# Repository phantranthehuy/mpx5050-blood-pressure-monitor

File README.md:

# 🩺 Digital Oscillometric Blood Pressure Monitor

> An academic research project focused on designing and developing a digital blood pressure monitor using the **MPX5050** pressure sensor and the **Oscillometric Method**.

## 📖 Table of Contents
- [About the Project](#about-the-project)
- [Key Features](#key-features)
- [Team Members](#team-members)
- [System Architecture](#system-architecture)
- [Technology Stack](#technology-stack)
- [Repository Structure](#repository-structure)
- [Getting Started](#getting-started)
- [License](#license)

## 🔬 About the Project
This repository contains the hardware schematics, embedded C firmware, and signal processing algorithms for an automated blood pressure monitor. 

The system operates based on the **Oscillometric Method**. It extracts tiny pressure oscillations (AC component) superimposed on the static cuff pressure (DC component) during the deflation phase. By analyzing the envelope of these oscillations, the system calculates the Mean Arterial Pressure (MAP), Systolic Pressure (SYS), Diastolic Pressure (DIA), and Heart Rate (BPM).

## ✨ Key Features
- **Automated Cuff Control:** Smooth inflation and linear deflation using a DC pump and a solenoid valve.
- **High-Precision Sensing:** Utilizes the MPX5050DP sensor with a custom Analog Front-End (AFE) for signal amplification and band-pass filtering (0.5Hz - 5Hz).
- **DSP Algorithms:** Implements digital filtering and envelope detection algorithms to accurately identify blood pressure parameters.
- **User Interface:** Real-time pressure monitoring and final result display via an LCD/OLED screen.

## 👥 Team Members
| Name | Role | Responsibilities |
| :--- | :--- | :--- |
| **Phan Tran The Huy** | **Project Manager & Hardware Lead** | Overall project management, Altium/KiCad schematic & PCB design, and hardware integration. |
| **Tran Nhat Ly** | **Mechanical & UI/UX Engineer** | 3D enclosure design, mechanical assembly, component sourcing, and UI programming. |
| **Nguyen Huy Hoang** | **DSP Algorithm & Research Lead** | Signal processing research (Kalman/FIR filters), data analysis, and technical documentation. |
| **Cao Hoang Tung** | **Embedded Software Engineer** | STM32 C programming, Pump/Valve driver implementation, and translating MATLAB/Python algorithms into embedded C. |

## 📐 System Architecture

The core of the system relies on capturing and separating the pressure signals:

## 🛠 Technology Stack
- **Microcontroller:** STM32 Series
- **Firmware:** C (STM32 HAL, CMake) trong `firmware/stm32-hal-cmake/`; tùy chọn C/C++ Arduino (STM32duino) trong `firmware/stm32-arduino-pio/`.
- **Development Environment:** VS Code with STM32CubeIDE Extension (HAL) hoặc VS Code + PlatformIO (Arduino, `firmware/stm32-arduino-pio/`).
- **Hardware Design:** Altium Designer / KiCad
- **Simulation Tools:** LTSpice (Analog filtering), Python/MATLAB (Algorithm verification)

## 📂 Repository Structure
```text
📦 mpx5050-blood-pressure-monitor
 ┣ 📂 Algorithms      # Python/MATLAB scripts for algorithm simulation & signal filtering
 ┣ 📂 Docs            # Datasheets, academic papers, and technical reports
 ┣ 📂 firmware        # stm32-hal-cmake (CMake+HAL) + stm32-arduino-pio (PlatformIO Arduino)
 ┣ 📂 Hardware        # Schematics, PCB layouts, and Bill of Materials (BOM)
 ┣ 📂 Mechanical      # 3D models and CAD files for the device enclosure
 ┣ 📜 .gitignore      # Ignored files for STM32, VS Code, and EDA tools
 ┣ 📜 LICENSE         # MIT License
 ┗ 📜 README.md       # Project documentation
```

## 🚀 Getting Started

### Prerequisites
- **VS Code** installed with the `C/C++` and `STM32 VS Code Extension`.
- **STM32CubeMX** (for modifying microcontroller pinouts/clocks).
- **Git** for version control.

### Installation & Build
1. **Clone the repository:**
   ```bash
   git clone https://github.com/your-username/mpx5050-blood-pressure-monitor.git
   ```
2. **Open the firmware (HAL / CMake):**
   Open the `firmware/stm32-hal-cmake` directory in VS Code (CMake + STM32 HAL).
3. **Optional — Arduino framework (same MCU):**
   Open `firmware/stm32-arduino-pio` in VS Code with the PlatformIO extension, or run `pio run` from that folder (see `firmware/stm32-arduino-pio/README.md`).
4. **Compile:**
   Press `Ctrl + Shift + B` (or use the STM32 extension build button) to compile the C code and generate the `.elf` / `.hex` files.
5. **Flash to MCU:**
   Connect your ST-Link debugger and click `Run > Start Debugging` (F5) to flash the firmware onto the STM32.

## ⚖️ License
This project is licensed under the **MIT License** - see the [LICENSE](LICENSE) file for details. Designed for academic and research purposes.

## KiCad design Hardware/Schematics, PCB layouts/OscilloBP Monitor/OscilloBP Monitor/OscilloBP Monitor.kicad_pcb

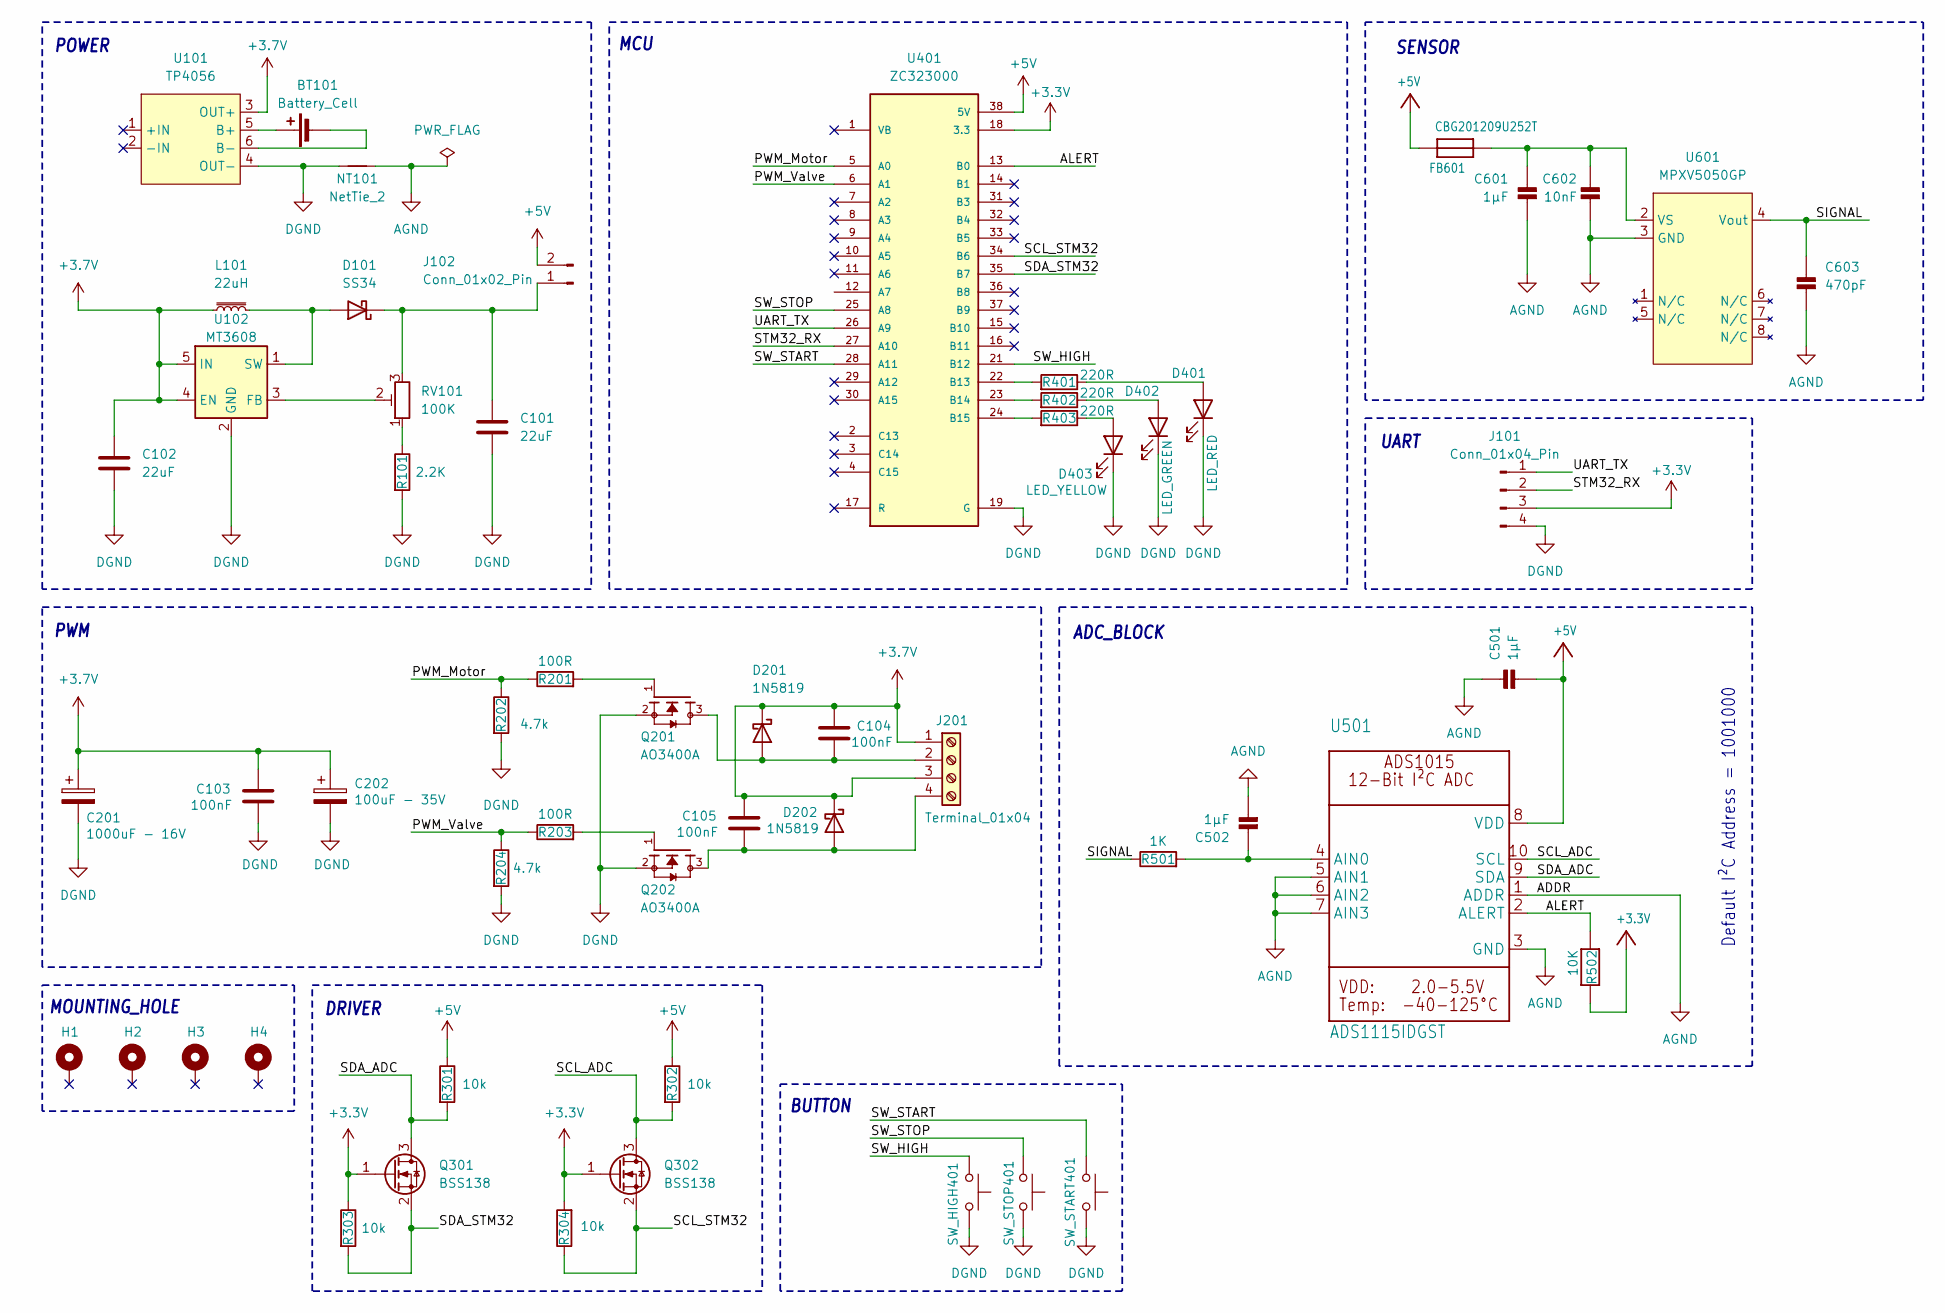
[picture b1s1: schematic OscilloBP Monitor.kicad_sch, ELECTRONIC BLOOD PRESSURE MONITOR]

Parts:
BT101: Battery_Cell; 1x18650
C101, C102: 22uF; C_1206_3216Metric_Pad1.33x1.80mm_HandSolder
C103, C104, C105: 100nF; C_1206_3216Metric_Pad1.33x1.80mm_HandSolder
C201: 1000uF - 16V; CP_Radial_D16.0mm_P7.50mm
C202: 100uF - 35V; CP_Radial_D6.3mm_P2.50mm
C501, C502, C601: 1µF; C_1206_3216Metric_Pad1.33x1.80mm_HandSolder
C602: 10nF; C_1206_3216Metric_Pad1.33x1.80mm_HandSolder
C603: 470pF; C_1206_3216Metric_Pad1.33x1.80mm_HandSolder
D101: SS34; D_SMA
D201, D202: 1N5819; D_DO-41_SOD81_P10.16mm_Horizontal
D401: LED_RED; LED_D3.0mm
D402: LED_GREEN; LED_D3.0mm
D403: LED_YELLOW; LED_D3.0mm
FB601: CBG201209U252T; L_0805_2012Metric_Pad1.05x1.20mm_HandSolder
H1, H2, H3, H4: MountingHole_Pad; mounting
J101: Conn_01x04_Pin; PinHeader_1x04_P2.54mm_Vertical
J102: Conn_01x02_Pin; PinHeader_1x02_P2.54mm_Vertical
J201: Terminal_01x04; PhoenixContact_GMSTBA_2,5_4-G-7,62_1x04_P7.62mm_Horizontal
L101: 22uH; CDRH104
NT101: NetTie_2; NetTie-2_THT_Pad0.3mm
Q201, Q202: AO3400A; SOT95P280X125-3N
Q301, Q302: BSS138; SOT-23
R101: 2.2K; R_1206_3216Metric_Pad1.30x1.75mm_HandSolder
R201, R203: 100R; R_1206_3216Metric_Pad1.30x1.75mm_HandSolder
R202, R204: 4.7k; R_1206_3216Metric_Pad1.30x1.75mm_HandSolder
R301, R302, R303, R304: 10k; R_1206_3216Metric_Pad1.30x1.75mm_HandSolder
R401, R402, R403: 220R; R_1206_3216Metric_Pad1.30x1.75mm_HandSolder
R501: 1K; R_1206_3216Metric_Pad1.30x1.75mm_HandSolder
R502: 10K; R_1206_3216Metric_Pad1.30x1.75mm_HandSolder
RV101: 100K; Potentiometer_Bourns_3296W_Vertical
SW_HIGH401: SW_Push; SW_PUSH_6mm_H4.3mm
SW_START401: SW_Push; SW_PUSH_6mm_H4.3mm
SW_STOP401: SW_Push; SW_PUSH_6mm_H4.3mm
U101: TP4056; TP4056_Module
U102: MT3608; SOT-23-6
U401: ZC323000; STM32F103C8T6; PARTREV N/A
U501: ADS1115IDGST; ADS1115_MSOP10
U601: MPXV5050GP; SOIC127P600X175-8N

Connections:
+3.3V: J101.3, Q301.1 (G), Q302.1 (G), R303.1, R304.2, R502.2, U401.18 (3.3), U401.40 (3.3)
+3.7V: C102.1, C103.1, C104.1, C105.1, C201.1, C202.1, D201.1 (K), D202.1 (K), J201.1, J201.3, L101.1, U101.3 (OUT+), U102.4 (EN), U102.5 (IN)
+5V: C501.2, FB601.2, J102.2, R301.1, R302.1, U401.38 (5V), U501.8 (VDD)
/ALERT: R502.1, U401.13 (B0), U501.2 (ALERT)
/PWM_Motor: R201.1, R202.1, U401.5 (A0)
/PWM_Valve: R203.1, R204.1, U401.6 (A1)
/SCL_ADC: Q302.3 (D), R302.2, U501.10 (SCL)
/SCL_STM32: Q302.2 (S), R304.1, U401.34 (B6)
/SDA_ADC: Q301.3 (D), R301.2, U501.9 (SDA)
/SDA_STM32: Q301.2 (S), R303.2, U401.35 (B7)
/SIGNAL: C603.1, R501.1, U601.4 (Vout)
/STM32_RX: J101.2, U401.27 (A10)
/SW_HIGH: SW_HIGH401.1, U401.21 (B12)
/SW_START: SW_START401.1, U401.28 (A11)
/SW_STOP: SW_STOP401.1, U401.25 (A8)
/UART_TX: J101.1, U401.26 (A9)
AGND: C501.1, C502.2, C601.2, C602.2, C603.2, NT101.2, U501.1 (ADDR), U501.3 (GND), U501.5 (AIN1), U501.6 (AIN2), U501.7 (AIN3), U601.3 (GND)
DGND: C101.2, C102.2, C103.2, C201.2, C202.2, D401.1 (K), D402.1 (K), D403.1 (K), J101.4, NT101.1, Q201.2, Q202.2, R101.2, R202.2, R204.2, SW_HIGH401.2, SW_START401.2, SW_STOP401.2, U101.4 (OUT-), U102.2 (GND), U401.19 (G), U401.20 (G), U401.39 (G)
unnamed: BT101.1 (+), U101.5 (B+)
unnamed: BT101.2 (-), U101.6 (B-)
unnamed: C502.1, R501.2, U501.4 (AIN0)
unnamed: C601.1, C602.1, FB601.1, U601.2 (VS)
unnamed: D101.2 (A), L101.2, U102.1 (SW)
unnamed: C101.1, D101.1 (K), J102.1, RV101.3
unnamed: C104.2, D201.2 (A), J201.2, Q201.3
unnamed: C105.2, D202.2 (A), J201.4, Q202.3
unnamed: D401.2 (A), R401.1
unnamed: D402.2 (A), R402.1
unnamed: D403.2 (A), R403.1
unnamed: Q201.1, R201.2
unnamed: Q202.1, R203.2
unnamed: R101.1, RV101.1
unnamed: RV101.2, U102.3 (FB)
unnamed: R401.2, U401.22 (B13)
unnamed: R402.2, U401.23 (B14)
unnamed: R403.2, U401.24 (B15)

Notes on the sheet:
BUTTON
SENSOR
PWM
MCU
ADC_BLOCK
Default I²C Address = 1001000
MOUNTING_HOLE
DRIVER
POWER
UART

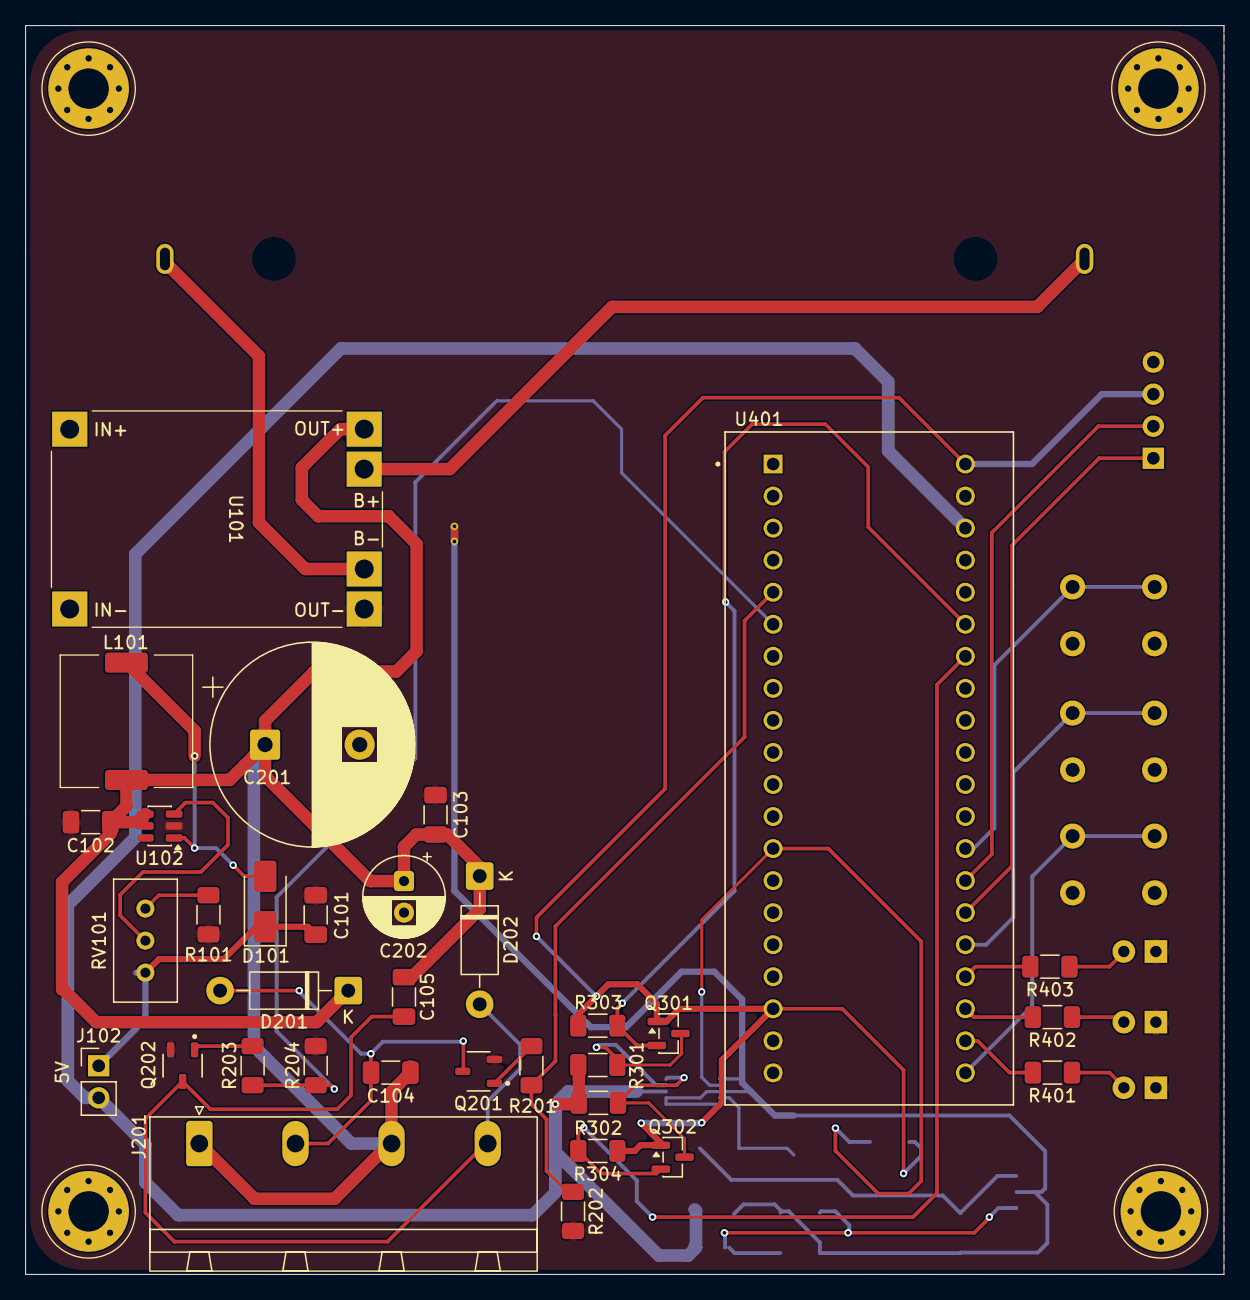
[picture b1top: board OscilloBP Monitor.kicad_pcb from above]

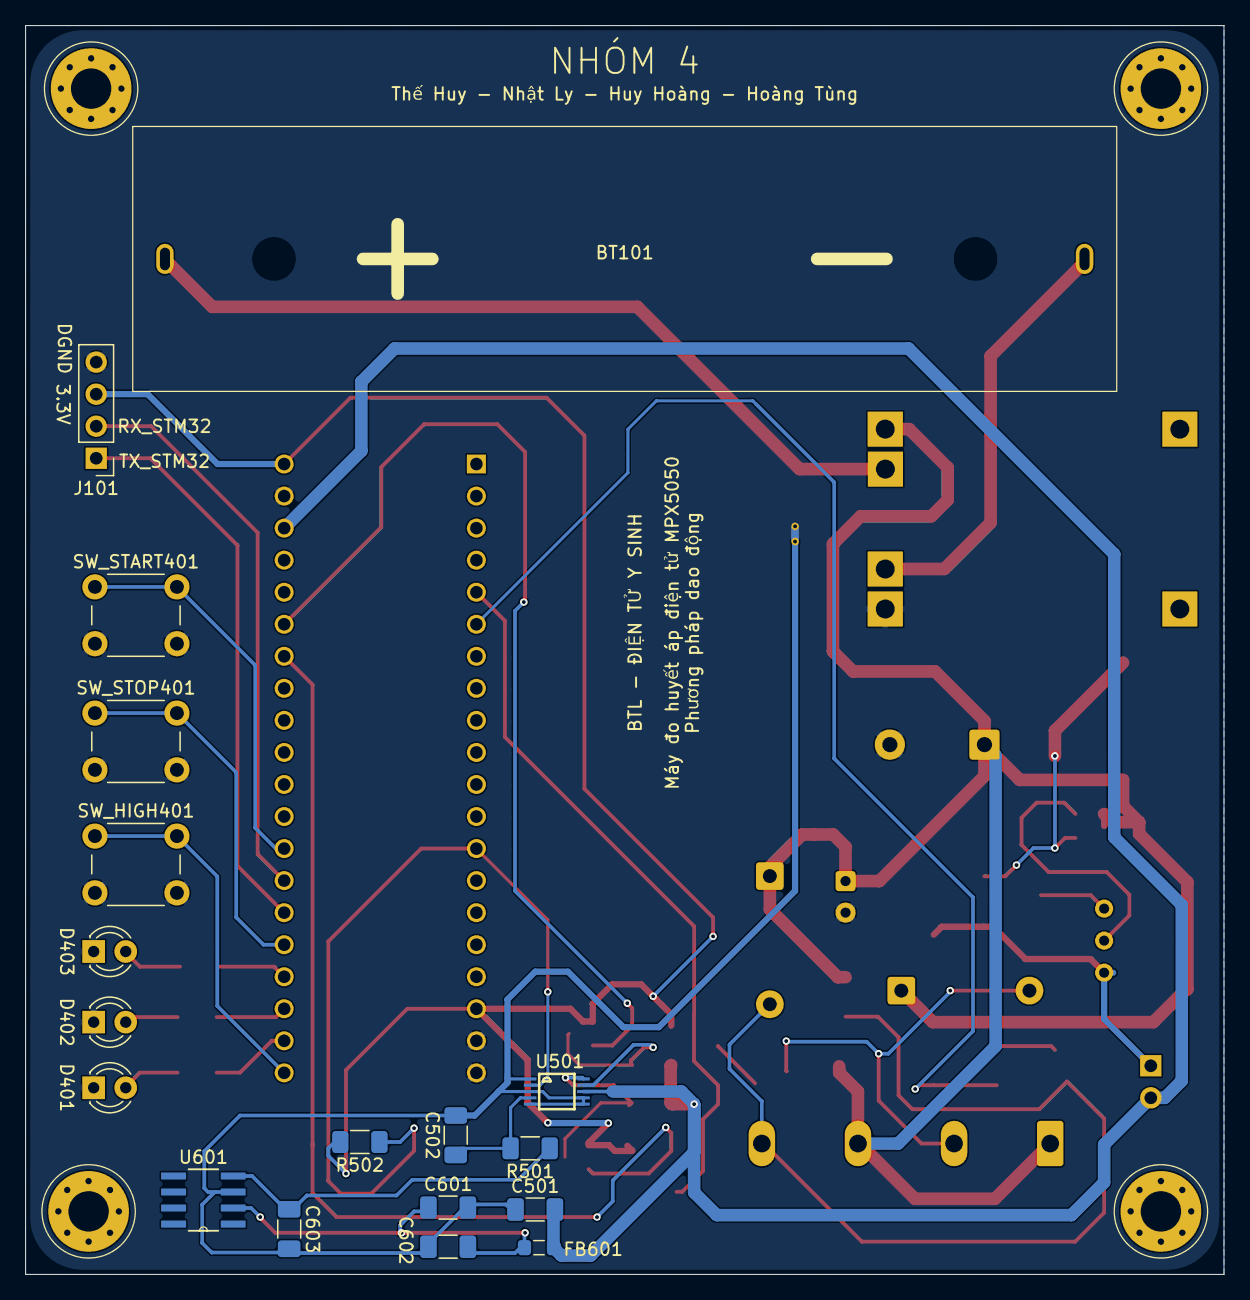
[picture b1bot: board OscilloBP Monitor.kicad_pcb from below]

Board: 2 copper layers, 95.0 x 99.0 mm, 56 parts (18 on the bottom side), 36 nets.

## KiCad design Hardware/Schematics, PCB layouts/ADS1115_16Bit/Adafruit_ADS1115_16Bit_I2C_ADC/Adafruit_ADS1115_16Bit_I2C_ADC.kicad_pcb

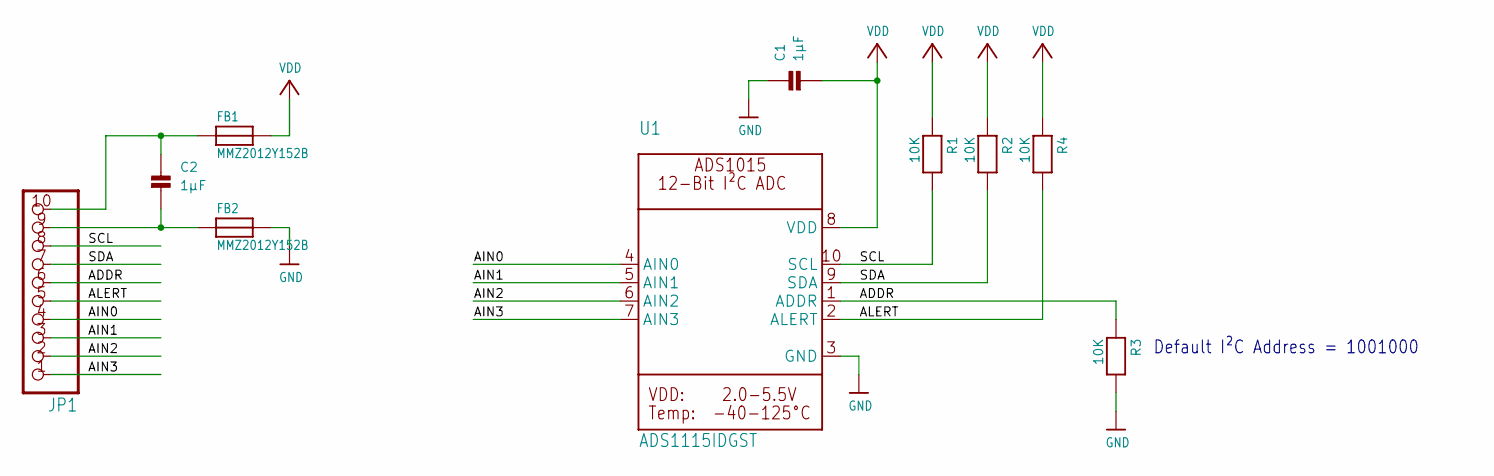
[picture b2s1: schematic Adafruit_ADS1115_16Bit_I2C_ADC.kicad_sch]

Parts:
C1, C2: 1µF; 0805
FB1, FB2: MMZ2012Y152B; 0805
JP1: HEADER-1X1070MIL; 1X10_ROUND70
R1, R2, R3, R4: 10K; 0805
U1: ADS1115IDGST; MSOP10

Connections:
ADDR: JP1.6, R3.1, U1.1 (ADDR)
AIN0: JP1.4, U1.4 (AIN0)
AIN1: JP1.3, U1.5 (AIN1)
AIN2: JP1.2, U1.6 (AIN2)
AIN3: JP1.1, U1.7 (AIN3)
ALERT: JP1.5, R4.2, U1.2 (ALERT)
GND: C1.1, FB2.2, R3.2, U1.3 (GND)
unnamed: C2.1, FB1.1, JP1.10
unnamed: C2.2, FB2.1, JP1.9
SCL: JP1.8, R1.2, U1.10 (SCL)
SDA: JP1.7, R2.2, U1.9 (SDA)
VDD: C1.2, FB1.2, R1.1, R2.1, R4.1, U1.8 (VDD)

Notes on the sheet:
Default I²C Address = 1001000

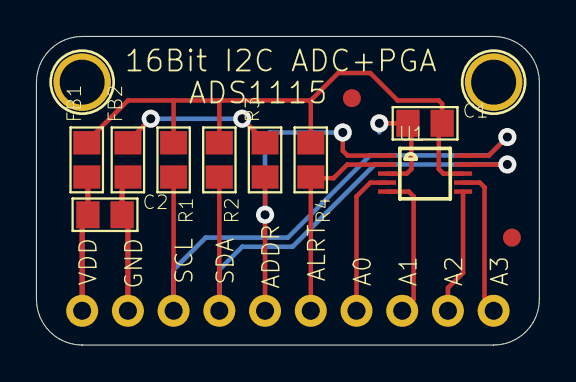
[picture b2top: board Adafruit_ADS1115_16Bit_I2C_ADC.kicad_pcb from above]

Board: 2 copper layers, 27.9 x 17.1 mm, 14 parts (0 on the bottom side), 12 nets.

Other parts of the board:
FID1, FID2: FIDUCIAL""; FIDUCIAL_1MM
U$13, U$14: MOUNTINGHOLE2.5; MOUNTINGHOLE_2.5_PLATED

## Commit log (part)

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2026-03-20 Create .gitignore for multiple development environments
    Added a comprehensive .gitignore file for C/C++, STM32, Altium Designer, KiCad, LTSpice, and general OS files.
2026-03-20 Revise README for project overview and setup
    Updated README to include detailed project information, features, team members, and setup instructions.
2026-03-20 Create CONTRIBUTING.md for team guidelines
    Added a contributing guide for the team to manage GitHub usage effectively.
2026-03-20 Enhance CONTRIBUTING.md with clearer GitHub usage steps
    Updated instructions for using GitHub Desktop and committing changes.
2026-03-20 Update CONTRIBUTING.md with new guidelines
2026-03-20 Change repository URL in CONTRIBUTING.md
    Updated the repository URL in the CONTRIBUTING.md file.
2026-03-21 Tạo file word thử
2026-03-21 Firmware
2026-03-21 tạo folder
2026-03-21 test nha chat
2026-03-22 Tìm linh kiện upload
2026-04-03 Thêm schematic.pdf
2026-04-03 Revise GitHub usage guidelines for team
    Updated the guidelines for using GitHub, including rules for branches, daily workflow, and pull requests.
2026-05-12 debug(uart): include ADC counts in sample stream
2026-05-12 hw(pins): remap buttons/PWM and move 100Hz tick to TIM3
    - Buttons → PA11/PA8/PB12, PWM bơm/van → PA0/PA1 (TIM2_CH1/CH2).
    - Đổi tick 100 Hz từ TIM2 sang TIM3 vì TIM2 nay phục vụ analogWrite()
    cho PWM 1 kHz trên PA0/PA1. Thứ tự setup: analogWriteFrequency() trước,
    rồi mới HardwareTimer(TIM3) để tránh reconfig nhầm timer của tick.
2026-05-12 feat(fsm): pump soft-start and slope cap to mitigate brownout
    Khi motor bơm khởi động kéo dòng inrush gấp 5-10 lần dòng chạy,
    nguồn không đủ gồng sẽ kéo VCC sụt < 3V → STM32 brownout-reset.
    Thêm 3 giới hạn trong bp_fsm.c để giảm di/dt và đỉnh dòng:
    - IDLE→INFLATE: kick khởi đầu giảm từ 15% xuống PUMP_PWM_MIN (5%).
    - Soft-start window: trong PUMP_SOFTSTART_MS (500ms) đầu sau khi rời
    IDLE, kẹp pump_pwm ≤ PUMP_SOFTSTART_CAP_PCT (30%).
2026-05-12 debug(stream): include FSM state, PWM and buttons in S,... line
    Dòng S,... mở rộng thành
    S,seq,t_ms,p_mmHg,rc,counts,fsm,pump%,valve%,btnSPH
    để mỗi tick đều thấy trạng thái FSM, PWM bơm/van và 3 nút (đã đảo
    active-low). Hỗ trợ chẩn đoán hiện tượng "bấm START mà motor không
    chạy" — phân biệt được rơi vào state nào (FAST_DEFLATE do STOP stuck,
    ERROR do I2C, hay đang INFLATE nhưng PWM không lên do nguồn).
